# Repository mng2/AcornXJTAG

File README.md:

# AcornXJTAG
This is a small PCB for connecting the SQRL Acorn JTAG to a Xilinx pod. Tested with the first-generation Xilinx Platform Cable USB, manufactured via OSHPark.

## Bill of Materials
1. Pico-EZmate 6-pin, Molex 0781715006, Digi-Key WM5408CT-ND
1. 2x7 2mm receptacle, Molex 0787881414, Digi-Key WM26519-ND
1. Pico-EZmate 6-wire assembly 15cm, Molex 0369200602, Digi-Key WM26623-ND (other lengths available)

## Notes
* The Pico-EZmate connector is not really designed for hand soldering, 
but it doesn't really make sense to bother with a solder stencil for this board either.
The ones I soldered by hand, are pushed over slightly to give the soldering iron some room to work,
so the anchors are not accessible. I was too lazy to modify the footprint, which is an option. 
Otherwise I recommend adding glue or epoxy.
* The 2mm connector that comes with the OEM Xilinx flying-wire adapter is pretty tall.
I tried to find a similarly dimensioned connector but was unable to identify one that is commonly stocked.
The one specified here is widely available and seems to make good enough contact
with my Xilinx pod, but of course YMMV.
* This is revB since apparently I made revA under covid brain and forgot
that the Pico-EZmate cable assemblies are wired in a way that flips the connections...

## License
CERN OHL Permissive v2

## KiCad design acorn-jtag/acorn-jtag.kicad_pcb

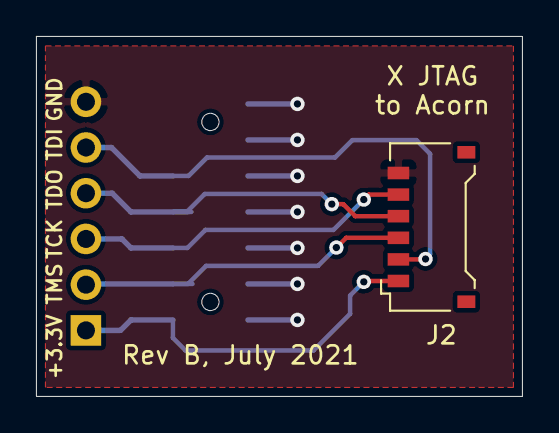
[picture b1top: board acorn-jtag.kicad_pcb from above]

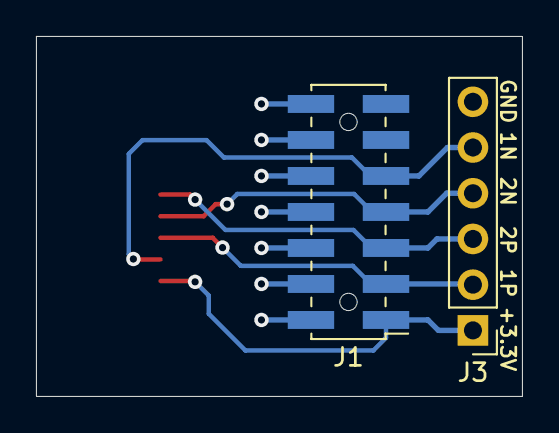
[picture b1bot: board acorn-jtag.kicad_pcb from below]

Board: 2 copper layers, 27.0 x 20.0 mm, 3 parts (2 on the bottom side), 6 nets.

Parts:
J1: Xilinx JTAG 2mm; Pin_Header_Straight_2x07_Pitch2.00mm_SMD_NPTH
J2: Pico-EZMate; Molex_Pico-EZmate_06x1.20mm_Angled
J3: Breadboard 0.1"; Pin_Header_Straight_1x06_Pitch2.54mm

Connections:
/TCK: J1.5, J2.5, J3.3
/TDI: J1.9, J2.2, J3.5
/TDO: J1.7, J2.4, J3.4
/TMS: J1.3, J2.3, J3.2
/Vref: J1.1, J2.1, J3.1
GND: J1.2, J1.4, J1.6, J1.8, J1.10, J1.12, J1.14, J2.6, J3.6

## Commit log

2021-08-16 add project files
2021-08-16 add pics
2021-08-16 edit wording
2021-08-16 adjustments
2021-08-30 editing readme
